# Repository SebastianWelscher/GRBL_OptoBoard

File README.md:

# GRBL_OptoBoard

Based on the schematics from https://github.com/gnea/grbl/wiki/Wiring-Limit-Switches, here with mostly smd parts. 
You can order the PCB on Aisler https://aisler.net/p/MWZMTXNJ. 

To power the hole PCB over one 5V connection, make a bridge between pad 2 and 3. For seperate power on the left side, use the additional connectors on the top and make a bridge between pad 1 and 2.

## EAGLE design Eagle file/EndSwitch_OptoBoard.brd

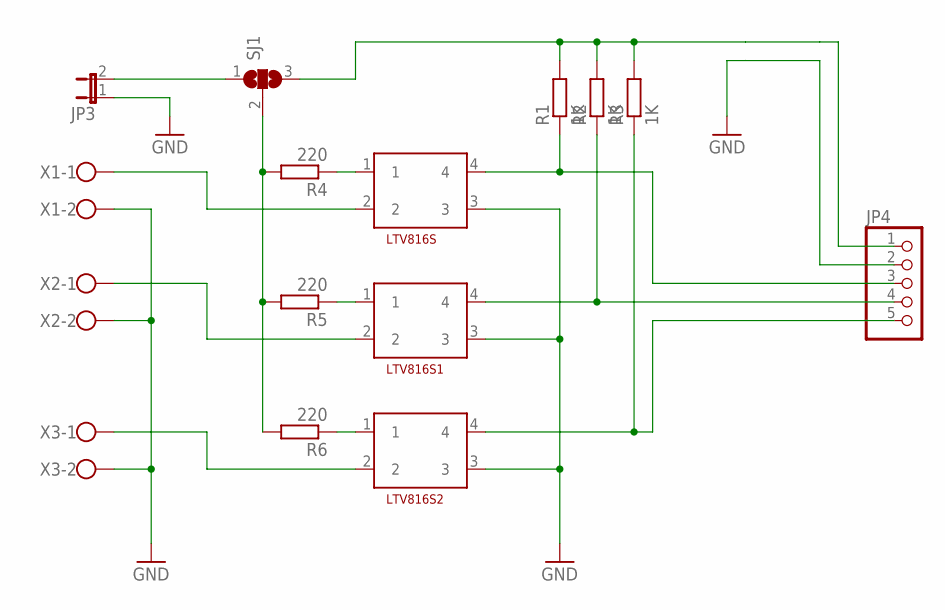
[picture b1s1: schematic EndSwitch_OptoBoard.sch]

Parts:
JP3: JP1E; JP1
JP4: PINHD-1X5; 1X05
LTV816S, LTV816S1, LTV816S2: LTV816S
R1, R2, R3: 1K; R0603
R4, R5, R6: 220; R0603
SJ1: SJ2W; SJ_2
X1, X2, X3: W237-102

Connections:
GND: JP3.1, JP4.2, LTV816S.3, LTV816S1.3, LTV816S2.3, X1.2, X2.2, X3.2
unnamed: LTV816S.1, R4.1
unnamed: LTV816S1.1, R5.1
unnamed: LTV816S2.1, R6.1
unnamed: LTV816S2.2, X3.1
unnamed: LTV816S1.2, X2.1
unnamed: LTV816S.2, X1.1
unnamed: R4.2, R5.2, R6.2, SJ1.2
unnamed: JP3.2, SJ1.1
unnamed: JP4.1, R1.2, R2.2, R3.2, SJ1.3
unnamed: JP4.3, LTV816S.4, R1.1
unnamed: JP4.4, LTV816S1.4, R2.1
unnamed: JP4.5, LTV816S2.4, R3.1

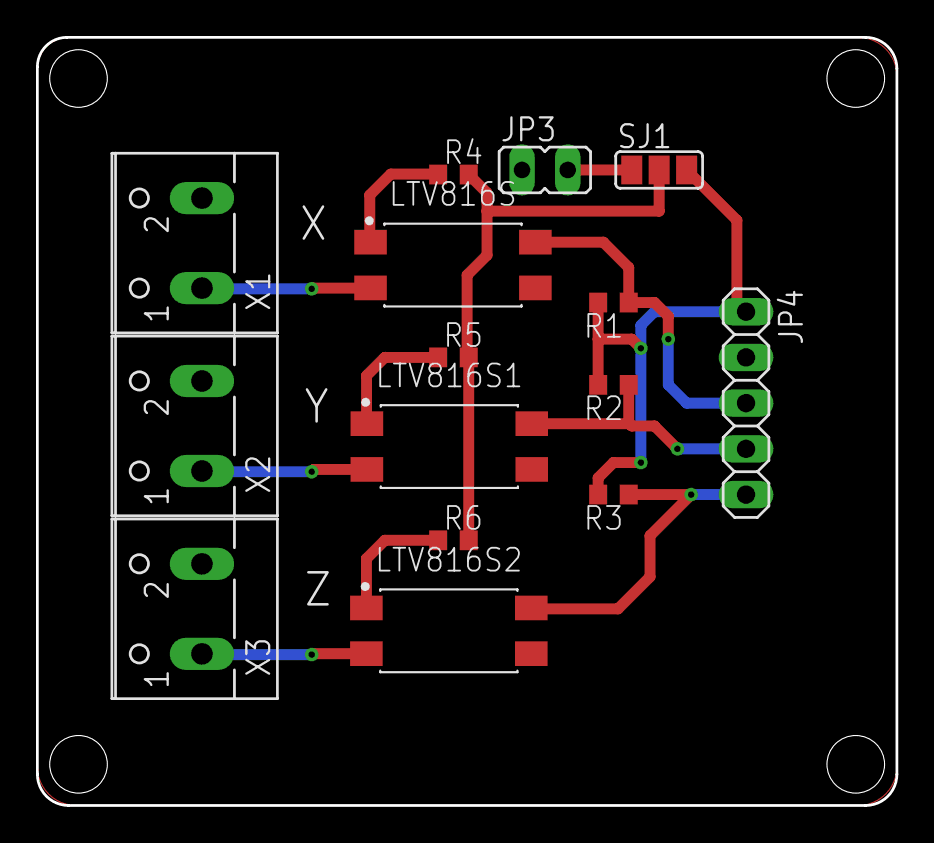
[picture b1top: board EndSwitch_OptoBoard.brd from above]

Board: 2 copper layers, 47.8 x 42.7 mm, 15 parts (0 on the bottom side), 13 nets.

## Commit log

2018-10-01 Create images
2018-10-01 Create board
2019-03-30 Create LICENSE
2019-03-30 Create Licence
2019-03-30 Set theme jekyll-theme-architect
